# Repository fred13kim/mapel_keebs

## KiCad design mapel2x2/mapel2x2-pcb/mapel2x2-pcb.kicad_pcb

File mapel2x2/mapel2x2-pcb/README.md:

| Component | Quantity | Package | Sample Part |
| --------------- | --------------- | --------------- | --------------- |
| Ceramic Capacitor, 0.1uF | 3 | 0805 | [1276-2444-1-ND] |
| Ceramic Capacitor, 10uF | 1 | 0805 | [1276-6455-1-ND] |
| Ceramic Capacitor, 1uF | 1 | 0805 | [1276-1066-1-ND] |
| Ceramic Capacitor, 22pF | 2 | 0805 | [1276-2605-1-ND] |
| Diode, Generic Capacitor | 4 | SOD-123 | [1N4148WTPMSCT-ND] |
| Polyfuse, 500mA hold, 1A trip | 1 | 1206 | [507-1803-1-ND] |
| Resistor, 10k | 2 | 0805 | [P10KAZCT-ND] |
| Resistor, 22 | 2 | 0805 | [P22ACT-ND] |
| Resistor, 5.1k | 2 | 0805 | [P5.1KDACT-ND] |
| Low Profile Tactile Switch | 1 | 5.2x5.2mm | [CKN10361CT-ND] |
| ATMEGA32UF MICROCONTROLLER | 1 | 44TQFP 10x10mm | [ATMEGA32U4-AU-ND] |
| GCT USB C Receptacle | 1 | USB4110-GF-A | [2073-USB4110-GF-A-1-ND] |
| Crystal, 16 MHz | 1 | 3.2x2.5mm, 4 pad | [478-CX3225SB16000D0GZJC1CT-ND] |

[1276-2444-1-ND]: https://www.digikey.com/short/5hhqzztt
[1276-6455-1-ND]: https://www.digikey.com/short/tjd3tcwv
[1276-1066-1-ND]: https://www.digikey.com/short/wdw7r1vq
[1276-2605-1-ND]: https://www.digikey.com/short/mpnt88d3
[1N4148WTPMSCT-ND]: https://www.digikey.com/short/5rzdmmrr
[507-1803-1-ND]: https://www.digikey.com/short/m49q8bp7
[P10KAZCT-ND]: https://www.digikey.com/short/7v1vtjcq
[P22ACT-ND]: https://www.digikey.com/short/q71zvf8j
[P5.1KDACT-ND]: https://www.digikey.com/short/9zjc58df
[CKN10361CT-ND]: https://www.digikey.com/short/z2pppj34
[ATMEGA32U4-AU-ND]: https://www.digikey.com/short/n8tv14mq
[2073-USB4110-GF-A-1-ND]: https://www.digikey.com/short/vww55r2c
[478-CX3225SB16000D0GZJC1CT-ND]: https://www.digikey.com/short/94qnrw87

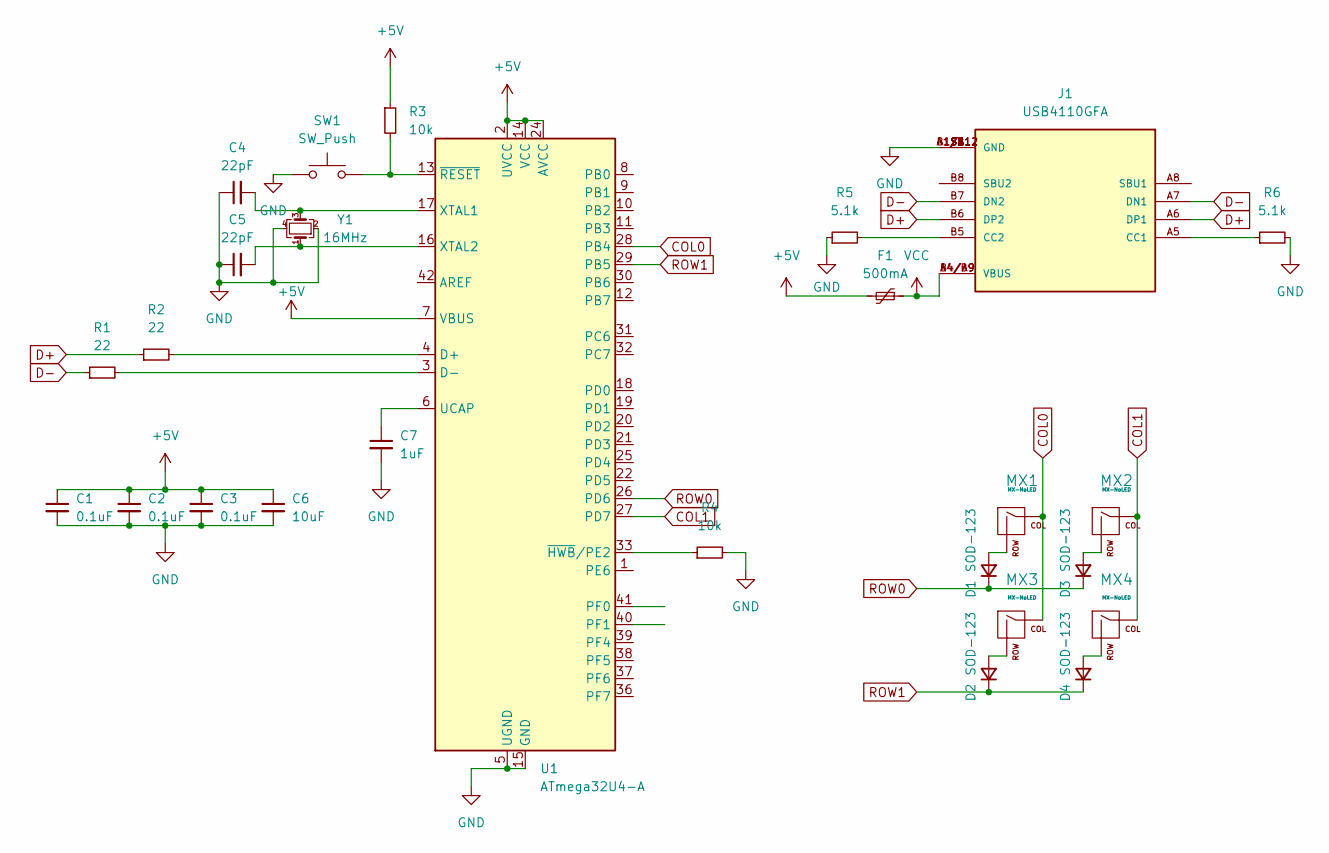
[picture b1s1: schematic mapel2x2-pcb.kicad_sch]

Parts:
C1, C2, C3: 0.1uF; C_0805_2012Metric
C4, C5: 22pF; C_0805_2012Metric
C6: 10uF; C_0805_2012Metric
C7: 1uF; C_0805_2012Metric
D1, D2, D3, D4: SOD-123; D_SOD-123
F1: 500mA; Fuse_1206_3216Metric
J1: USB4110GFA; GCT_USB4110GFA
MX1, MX2, MX3, MX4: MX-NoLED; MX-1U-NoLED
R1, R2: 22; R_0805_2012Metric
R3, R4: 10k; R_0805_2012Metric
R5, R6: 5.1k; R_0805_2012Metric
SW1: SW_Push; SKQG-1155865
U1: ATmega32U4-A; TQFP-44_10x10mm_P0.8mm
Y1: 16MHz; Crystal_SMD_3225-4Pin_3.2x2.5mm

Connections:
+5V: C1.1, C2.1, C3.1, C6.1, F1.2, R3.1, U1.2 (UVCC), U1.7 (VBUS), U1.14 (VCC), U1.24 (AVCC), U1.34 (VCC), U1.44 (AVCC)
COL0: MX1.1 (COL), MX3.1 (COL), U1.28 (PB4)
COL1: MX2.1 (COL), MX4.1 (COL), U1.27 (PD7)
D+: J1.A6 (DP1), J1.B6 (DP2), R2.1
D-: J1.A7 (DN1), J1.B7 (DN2), R1.1
GND: C1.2, C2.2, C3.2, C4.1, C5.1, C6.2, C7.2, J1.A1/B12 (GND), J1.B1/A12 (GND), J1.S1 (GND), J1.S2 (GND), J1.S3 (GND), J1.S4 (GND), R4.2, R5.1, R6.2, SW1.1, U1.5 (UGND), U1.15 (GND), U1.23 (GND), U1.35 (GND), U1.43 (GND), Y1.2, Y1.4
unnamed: C4.2, U1.17 (XTAL1), Y1.3
unnamed: C5.2, U1.16 (XTAL2), Y1.1
unnamed: C7.1, U1.6 (UCAP)
unnamed: D1.2 (A), MX1.2 (ROW)
unnamed: D2.2 (A), MX3.2 (ROW)
unnamed: D3.2 (A), MX2.2 (ROW)
unnamed: D4.2 (A), MX4.2 (ROW)
unnamed: J1.A5 (CC1), R6.1
unnamed: J1.B5 (CC2), R5.2
unnamed: R1.2, U1.3 (D-)
unnamed: R2.2, U1.4 (D+)
unnamed: R3.2, SW1.2, U1.13 (~RESET)
unnamed: R4.1, U1.33 (~HWB/PE2)
ROW0: D1.1 (K), D3.1 (K), U1.26 (PD6)
ROW1: D2.1 (K), D4.1 (K), U1.29 (PB5)
VCC: F1.1, J1.A4/B9 (VBUS), J1.B4/A9 (VBUS)

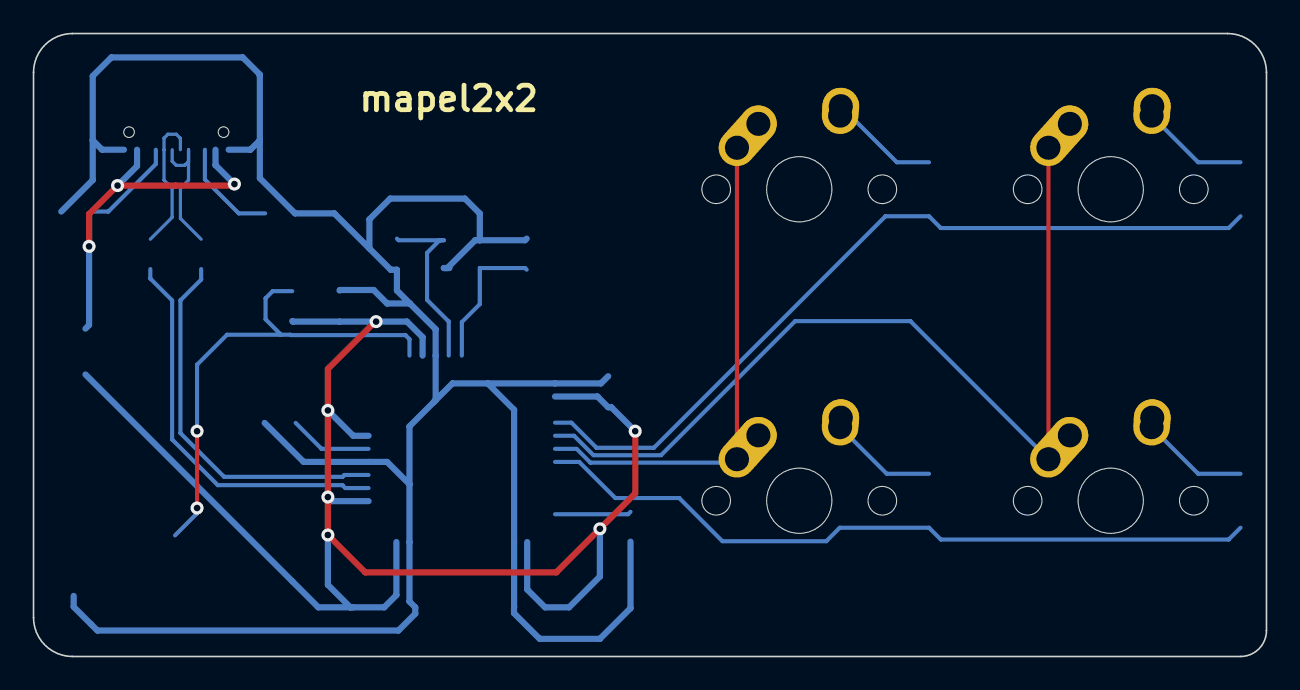
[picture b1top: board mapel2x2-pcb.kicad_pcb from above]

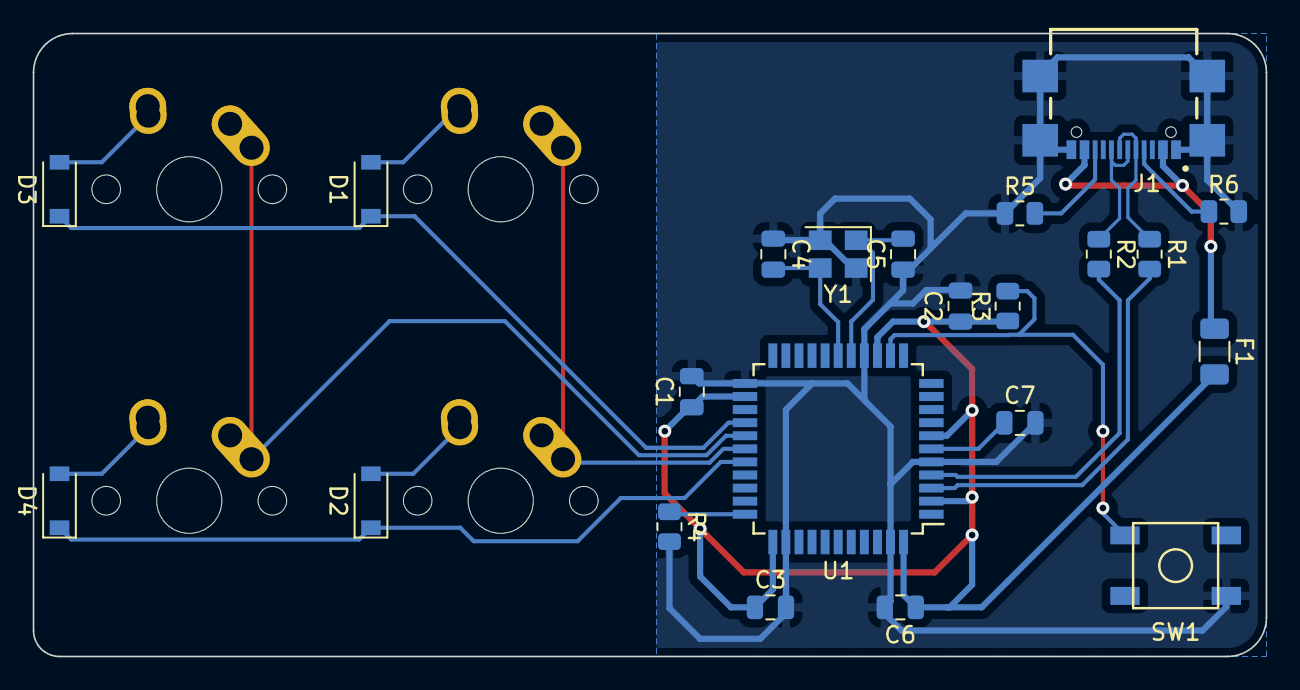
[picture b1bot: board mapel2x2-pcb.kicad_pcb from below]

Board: 2 copper layers, 75.4 x 38.1 mm, 26 parts (22 on the bottom side), 22 nets.

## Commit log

2024-07-14 Add mapel2x2
2024-07-23 move footprints into designated footprint directory
2024-07-23 mapel-leaf pcb initial commit
2024-07-23 add better USB-C footprint
2024-07-23 add some basic keeb stuff including beginning of sch
